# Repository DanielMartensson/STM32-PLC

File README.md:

# STM32 PLC

This project is a PCB bord that has the following measurement and control input/output:

 * 12 x ADC at 16-bit resolution for 0-20mA input with programmable gain
 * 5 x Differential ADC at 16-bit for 0-20mA input with programmable gain
 * 3 x DAC at 12-bit with 0-20mA output
 * 8 x PWM for 0-2.2A with N-channel MOSFET
 * 10 x Digital Input
 * 1 x CAN-bus channel
 * 4 x Input Capture for 0 kHz to 10kHz
 * 3 x Encoder for -32768 to 32767 pulses
 * 1 x USB port for connecting with [OpenSourceLogger](https://github.com/DanielMartensson/OpenSourceLogger) and [GoobySoft](https://github.com/DanielMartensson/GoobySoft)
 * 1 x SPI with 3 chip select for ILI9341 LCD with touch
 * 1 x ST-Link V2 connection
 * 1 x RTC clock with two alarms A(date) and B(week day) and a battery holder so the RTC remembers the date and time

## Protection 
 * All ADC, Digital Input, Differential ADC, Input Capture and Encoder are high voltage protected with PTC(fall current 30mA) fuse + 3.6v zener diode.
 * All PWM and DAC are high voltage protected with N-channel MOSFET and PNP-transistor and OP-amp. 
 * The CAN-bus channel is high voltage peak protected for 3000V under a short time with a TVS-diode. The CAN-bus transmitter itself can hold against -14V to +14V, but the TVS-diode has a limit around 6V. 

## Documentation
The documentation for the pin map can be found in the `Documentation` folder. Also all the article numbers for each component can be found in at the `DAC ADC PWM IO.sch` file in the `PCB` folder. Just double click on a PCB symbol and see the `Mouser Electronics` article number of the electrical component. 

## Calibration
Yes, it's possible to set the calibration to each input in this project. You need to have the ILI9341 touch LCD with SPI bus. Open the `STM32 PLC Pinouts.pdf` and see the connection for the LCD. You can also set the PWM frequency and analog input gain for the ADC and Differential ADC at 16-bit. 

## SAE J1939
The STM32 PLC has internal SAE J1939 protocol. Made from [Open-SAE-J1939](https://github.com/DanielMartensson/Open-SAE-J1939) repository.

## OpenSourceLogger
This is a QT C++ software that you can connect to your STM32 PLC board via the USB and then you can send signals from OpenSourceLogger and recieve signals.
OpenSourceLogger is a very easy to use logging and controlling software and it stores data at a SQL server. 

## GoobySoft
This is a ImGui C++ project that do the same as OpenSourceLogger, but it's much better and have more features. The reason why I moved away from QT C++ to ImGui C++ is because
it's much easier to write a GUI application in C++ by using ImGui instead of QT. With QT, you are stuck with object oriented programming. Everything is a class. 
But for ImGui, you can choose which type of lever you want to code, I prefer C-style C++ code with a small dose of object oriented programming (if needed). 

Consider that I will work on GoobySoft instead of OpenSourceLogger.

## Program 
The STM32 PLC has a lot of functions you can select by touching the LCD. 

 * A:Show measurement and time
 * B:Set analog gain
 * C:Set PWM frequencies
 * D:Set analog input calibration
 * E:Set pulses per encoder revolution
 * F:Set date and time and alarm
 * G:Do a PGN request
 * H:Show ECU addresses
 * I:Commanded address
 * J:Show this ECU DM1 codes
 * K:Show other ECU DM1 codes
 * L:Show this ECU DM2 codes
 * M:Show other ECU DM2 codes
 * N:Show this ECU name
 * O:Show other ECU name
 * P:Show this ECU identifications
 * Q:Show other ECU identifications
 * R:SAE J1939 Auxiliary valve command
 * S:Analog in to PWM
 * T:Analog in to analog out
 * U:About STM32 PLC

## How to build this STM32 PLC

 1. Download this repository
 2. Download & Install KiCad
 3. Open the `PCB` folder and open the `.pro` file with KiCAD and greate a `gerber` file of your own choice
 4. Go to your PCB manufacturer and give them the `gerber` file and let them produce the board for you
 5. Order the eletrical components from `Mouser Electronics`
 6. Once you have the eletrical components and your PCB board, it's time to solder them.
 7. Once the PCB board is finished, then install STM32CubeIDE
 8. Open the `Code` project and import the `.ioc` project file using STM32CubeIDE
 9. Flash the board with the `C` code by using ST-Link V2 connection
 10. Connect the ILI9431 touch LCD and then you are done!

## Software used

 * KiCAD: 6.0.7
 * STM32CubeIDE 1.10.1

## Status of the project
It's done. I don't plan to update this project. Everything is working and it will remain that way.

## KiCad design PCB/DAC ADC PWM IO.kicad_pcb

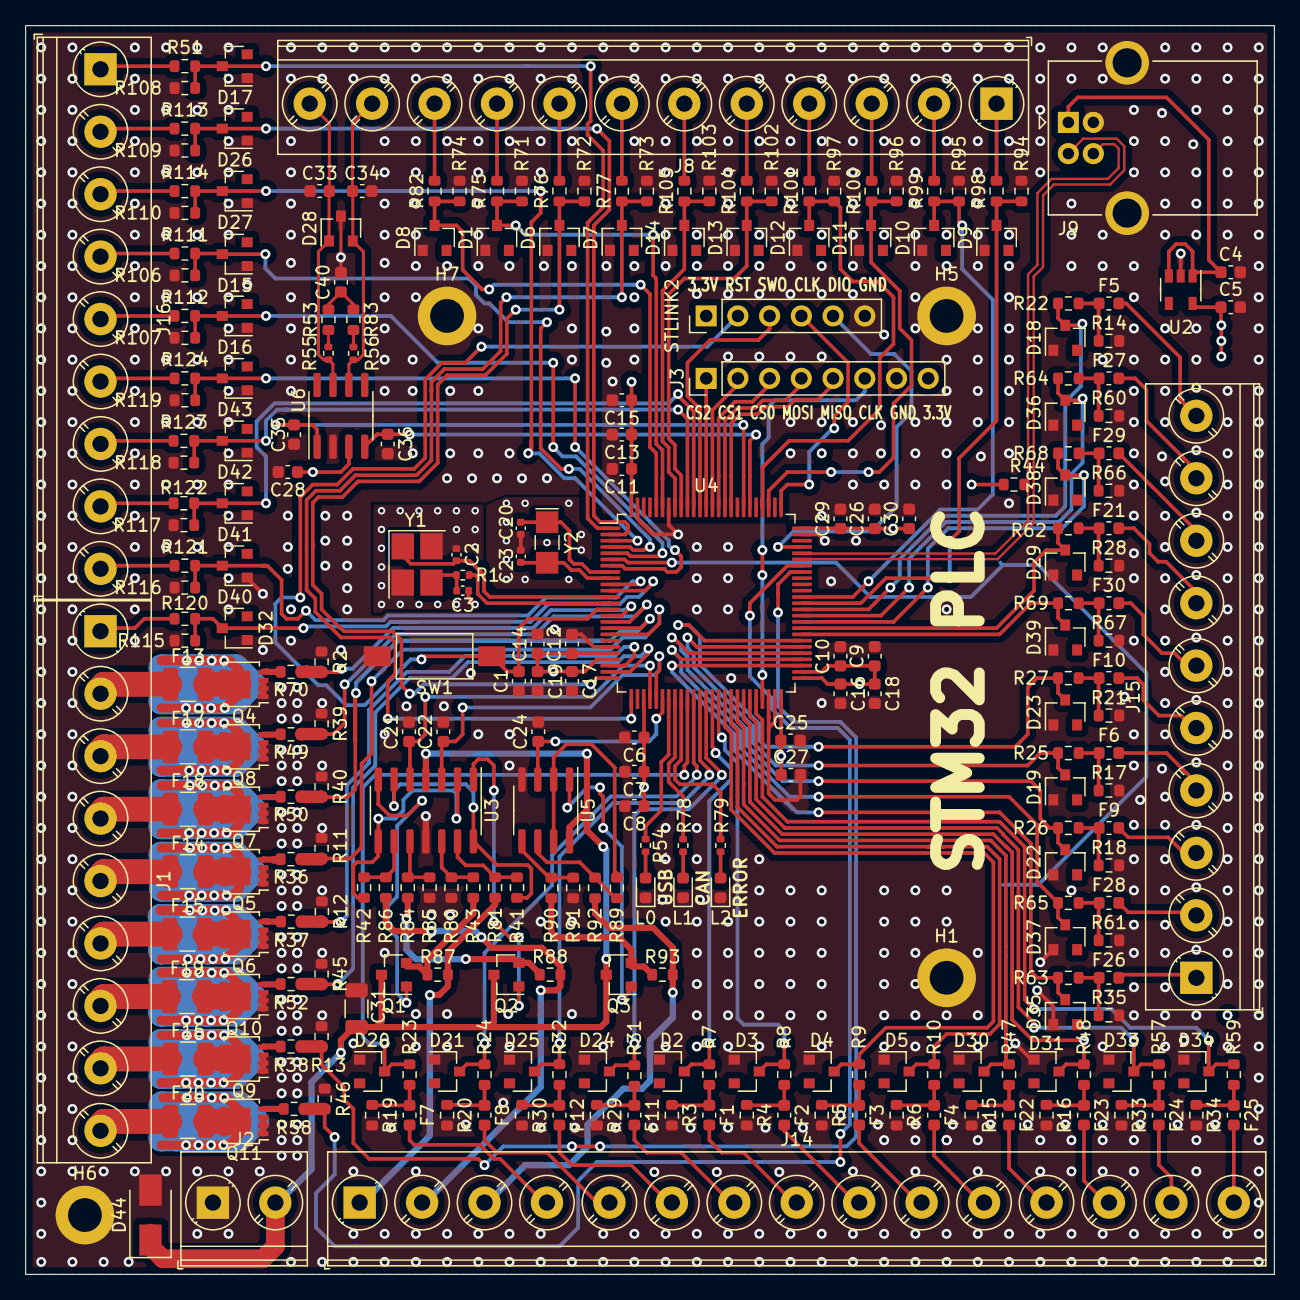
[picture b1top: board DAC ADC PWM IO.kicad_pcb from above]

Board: 4 copper layers, 100.0 x 100.0 mm, 270 parts (1 on the bottom side), 194 nets.

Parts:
BT1: Battery_Cell; BatteryHolder_Keystone_3002_1x2032
C1, C6, C7, C11, C13, C21, C22, C24, C26, C29: 100nF; C_0603_1608Metric
C2, C3: 10pF; C_0402_1005Metric
C4, C5, C9, C14, C18, C19, C27: 1uF; C_0603_1608Metric
C8, C15, C30: 4.7uF; C_0603_1608Metric
C10, C12, C16, C17, C25, C28, C33, C34, C35, C36, C40: 10nF; C_0603_1608Metric
C20, C23: 4.7pF; C_0402_1005Metric
C31: 10uF; C_1206_3216Metric
D1, D2, D3, D4, D5, D6, D7, D8, D9, D10, D11, D12, D13, D14, D15, D16, D17, D18, D19, D20, D21, D22, D23, D24, D25, D26, D27, D29, D30, D31, D32, D33, D34, D35, D36, D37, D38, D39, D40, D41, D42, D43: BZX84C3V6LT1G; D_SOT-23_ANK
D28: PESD5V0L2BT,215; SOT-23
D44: SK56A-LTP; D_SMA
F1, F2, F3, F4, F5, F6, F7, F8, F9, F10, F11, F12, F21, F22, F23, F24, F25, F26, F27, F28, F29, F30: Max 30mA; Fuse_0603_1608Metric
F13, F14, F15, F16, F17, F18, F19, F20: Max 2.5A; Fuse_1210_3225Metric
H1, H5, H6, H7: MountingHole_Pad; MountingHole_2.7mm_M2.5_DIN965_Pad
J1, J16: Screw_Terminal_01x9; TerminalBlock_Phoenix_PT-1,5-9-5.0-H_1x09_P5.00mm_Horizontal
J2: Screw_Terminal_01x02; TerminalBlock_Phoenix_PT-1,5-2-5.0-H_1x02_P5.00mm_Horizontal
J3: Conn_01x08; PinHeader_1x08_P2.54mm_Vertical
J8: Screw_Terminal_01x12; TerminalBlock_Phoenix_PT-1,5-12-5.0-H_1x12_P5.00mm_Horizont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
J9: USB_B; USB_B_OST_USB-B1HSxx_Horizontal
J14: Screw_Terminal_01x15; TerminalBlock_Phoenix_PT-1,5-15-5.0-H_1x15_P5.00mm_Horizont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
J15: Screw_Terminal_01x10; TerminalBlock_Phoenix_PT-1,5-10-5.0-H_1x10_P5.00mm_Horizont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
L0: LED_USB_RX_TX; LED_0603_1608Metric
L1: LED_CAN_RX_TX; LED_0603_1608Metric
L2: LED_ERROR; LED_0603_1608Metric
Q1, Q2, Q3: BC847C-QR; SOT-23
Q4, Q5, Q6, Q7, Q8, Q9, Q10, Q11: BUK9M15-60EX; LFPAK33
R1: 2k; R_0402_1005Metric
R2, R11, R12, R13, R39, R40, R41, R42, R43, R45, R46, R51, R62, R71, R72, R73, R74, R75, R76, R77, R80, R81, R82, R84, R85, R86, R89, R90, R91, R92, R94, R95, R96, R97, R98, R99, R100, R101, R102, R103, R104, R105, R106, R107, R108, R109, R110, R111, R112, R113, R114, R115, R116, R117, R118, R119, R120, R121, R122, R123, R124: 10k; R_0603_1608Metric
R3, R4, R5, R6, R7, R8, R9, R10, R14, R15, R16, R17, R18, R19, R20, R21, R22, R23, R24, R25, R26, R27, R28, R29, R30, R31, R32, R33, R34, R35, R36, R37, R38, R47, R48, R49, R50, R52, R57, R58, R59, R60, R61, R63, R64, R65, R66, R67, R68, R69, R70, R87, R88, R93: 160; R_0603_1608Metric
R44: 1.5k; R_0603_1608Metric
R53, R83: 60; R_0603_1608Metric
R54, R78, R79: 220; R_0402_1005Metric
R55, R56: 0; R_0402_1005Metric
STLINK2: ST-Link V2 connetor; PinHeader_1x06_P2.54mm_Vertical
SW1: SW_Push; SW_SPST_FSMSM
U2: AP7343-33W5-7; SOT-23-5
U3: LM2902; SOIC-14_3.9x8.7mm_P1.27mm
U4: STM32F373VBTx; LQFP-100_14x14mm_P0.5mm
U5: LM2904; SOIC-8_3.9x4.9mm_P1.27mm
U6: TCAN332; SOIC-8_3.9x4.9mm_P1.27mm
Y1: HSE; Crystal_SMD_3225-4Pin_3.2x2.5mm_HandSoldering
Y2: LSE; Crystal_SMD_EuroQuartz_EQ161-2Pin_3.2x1.5mm_HandSoldering

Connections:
+3V3: C5.1, C6.1, C7.1, C8.1, C9.1, C10.1, C11.1, C12.1, C13.1, C14.1, C15.1, C16.1, C17.1, C18.1, C19.1, C25.1, C26.1, C27.1, C28.1, C29.1, C30.1, J3.8, R44.2, STLINK2.1, U2.5, U4.21, U4.22, U4.28, U4.50, U4.51, U4.52, U4.75, U4.100, U6.3
+5V: C4.1, J9.1, U2.1, U2.3
/CAN/CAN+: C33.2, D28.1, J8.12, R55.1, U6.7
/CAN/CAN-: C34.1, D28.2, J8.11, R56.2, U6.6
/DAC/AO0: J14.1, R81.2, R87.2
/DAC/AO1: J14.2, R86.2, R88.2
/DAC/AO2: J14.3, R92.2, R93.2
/DSDADC/DAI0M: F28.2, J15.2
/DSDADC/DAI0P: F26.2, J15.1
/DSDADC/DAI1M: F6.2, J15.4
/DSDADC/DAI1P: F9.2, J15.3
/DSDADC/DAI2M: F30.2, J15.6
/DSDADC/DAI2P: F10.2, J15.5
/DSDADC/DAI3M: F29.2, J15.8
/DSDADC/DAI3P: F21.2, J15.7
/DSDADC/DAI4M: F5.2, J15.10
/DSDADC/DAI4P: F27.2, J15.9
/Digital/P0: F13.1, J1.2
/Digital/P1: F17.1, J1.3
/Digital/P2: F18.1, J1.4
/Digital/P3: F14.1, J1.5
/Digital/P4: F15.1, J1.6
/Digital/P5: F19.1, J1.7
/Digital/P6: F16.1, J1.8
/Digital/P7: F20.1, J1.9
/INPUT/DI0: J16.1, R51.2
/INPUT/DI1: J16.2, R113.2
/INPUT/DI2: J16.3, R114.2
/INPUT/DI3: J16.4, R111.2
/INPUT/DI4: J16.5, R112.2
/INPUT/DI5: J16.6, R124.2
/INPUT/DI6: J16.7, R123.2
/INPUT/DI7: J16.8, R122.2
/INPUT/DI8: J16.9, R121.2
/INPUT/DI9: J1.1, R120.2
/Pulse/E0+: J8.6, R105.2
/Pulse/E0-: J8.5, R104.2
/Pulse/E1+: J8.4, R101.2
/Pulse/E1-: J8.3, R100.2
/Pulse/E2+: J8.2, R99.2
/Pulse/E2-: J8.1, R98.2
/Pulse/IC0: J8.10, R82.2
/Pulse/IC1: J8.9, R75.2
/Pulse/IC2: J8.8, R76.2
/Pulse/IC3: J8.7, R77.2
/SDADC/AI0: F7.2, J14.4
/SDADC/AI1: F8.2, J14.5
/SDADC/AI2: F12.2, J14.6
/SDADC/AI3: F11.2, J14.7
/SDADC/AI4: F1.2, J14.8
/SDADC/AI5: F2.2, J14.9
/SDADC/AI6: F3.2, J14.10
/SDADC/AI7: F4.2, J14.11
/SDADC/AI8: F22.2, J14.12
/SDADC/AI9: F23.2, J14.13
/SDADC/AI10: F24.2, J14.14
/SDADC/AI11: F25.2, J14.15
GND: BT1.2, C1.1, C2.1, C3.1, C4.2, C5.2, C6.2, C7.2, C8.2, C9.2, C10.2, C11.2, C12.2, C13.2, C14.2, C15.2, C16.2, C17.2, C18.2, C19.2, C20.1, C21.2, C22.2, C23.1, C24.2, C25.2, C26.2, C27.2, C28.2, C29.2, C30.2, C31.2, C33.1, C34.2, C35.1, C36.2, C40.2, D1.2, D2.2, D3.2, D4.2, D5.2, D6.2, D7.2, D8.2, D9.2, D10.2, D11.2, D12.2, D13.2, D14.2, D15.2, D16.2, D17.2, D18.2, D19.2, D20.2, D21.2, D22.2, D23.2, D24.2, D25.2, D26.2, D27.2, D28.3, D29.2, D30.2, D31.2, D32.2, D33.2, D34.2, D35.2, D36.2, D37.2, D38.2, D39.2, D40.2, D41.2, D42.2, D43.2, D44.2, H1.1, H5.1, H6.1, H7.1, J2.1, J3.7, J9.4, J9.5, L0.1, L1.1, L2.1, Q4.1, Q4.2, Q4.3, Q5.1, Q5.2, Q5.3, Q6.1, Q6.2, Q6.3, Q7.1, Q7.2, Q7.3, Q8.1, Q8.2, Q8.3, Q9.1, Q9.2, Q9.3, Q10.1, Q10.2, Q10.3, Q11.1, Q11.2, Q11.3, R2.2, R3.2, R4.2, R5.2, R6.2, R11.2, R12.2, R13.2, R14.2, R15.2, R16.2, R17.2, R18.2, R19.2, R20.2, R21.2, R28.2, R29.2, R30.2, R33.2, R34.2, R35.2, R39.2, R40.2, R45.2, R46.2, R60.2, R61.2, R66.2, R67.2, R71.1, R72.1, R73.1, R74.1, R80.1, R85.1, R91.1, R94.1, R95.1, R96.1, R97.1, R102.1, R103.1, R106.1, R107.1, R108.1, R109.1, R110.1, R115.1, R116.1, R117.1, R118.1, R119.1, STLINK2.6, SW1.1, U2.2, U3.11, U4.20, U4.48, U4.49, U4.74, U4.94, U4.99, U5.4, U6.2, Y1.2, Y1.4
NRST: C1.2, STLINK2.2, SW1.2, U4.14
unnamed: BT1.1, U4.6
unnamed: C3.2, R1.1, Y1.3
unnamed: C40.1, R53.2, R83.1
unnamed: F1.1, R3.1, R7.1
unnamed: F2.1, R4.1, R8.1
unnamed: F3.1, R5.1, R9.1
unnamed: F4.1, R6.1, R10.1
unnamed: F5.1, R14.1, R22.1
unnamed: F6.1, R17.1, R25.1
unnamed: F7.1, R19.1, R23.1
unnamed: F8.1, R20.1, R24.1
unnamed: F9.1, R18.1, R26.1
unnamed: F10.1, R21.1, R27.1
unnamed: F11.1, R29.1, R31.1
unnamed: F12.1, R30.1, R32.1
unnamed: F13.2, Q4.5
unnamed: F14.2, Q5.5
unnamed: F15.2, Q6.5
unnamed: F16.2, Q9.5
unnamed: F17.2, Q8.5
unnamed: F18.2, Q7.5
unnamed: F19.2, Q10.5
unnamed: F20.2, Q11.5
unnamed: F21.1, R28.1, R62.1
unnamed: F22.1, R15.1, R47.1
unnamed: F23.1, R16.1, R48.1
unnamed: F24.1, R33.1, R57.1
unnamed: F25.1, R34.1, R59.1
unnamed: F26.1, R35.1, R63.1
unnamed: F27.1, R60.1, R64.1
unnamed: F28.1, R61.1, R65.1
unnamed: F29.1, R66.1, R68.1
unnamed: F30.1, R67.1, R69.1
unnamed: L0.2, R54.2
unnamed: L1.2, R78.2
unnamed: L2.2, R79.2
unnamed: Q1.1, U3.7
unnamed: Q1.2, R43.2, R87.1
unnamed: Q2.1, U3.1
unnamed: Q2.2, R84.2, R88.1
unnamed: Q3.1, U5.1
unnamed: Q3.2, R90.2, R93.1
unnamed: Q4.4, R70.2
unnamed: Q5.4, R36.2
unnamed: Q6.4, R37.2
unnamed: Q7.4, R50.2
unnamed: Q8.4, R49.2
unnamed: Q9.4, R38.2
unnamed: Q10.4, R52.2
unnamed: Q11.4, R58.2
unnamed: R41.1, U3.6, U3.14
unnamed: R41.2, R81.1, U3.13
unnamed: R42.1, U3.2, U3.8
unnamed: R42.2, R86.1, U3.9
unnamed: R43.1, R80.2, U3.12
unnamed: R53.1, R55.2
unnamed: R56.1, R83.2
unnamed: R84.1, R85.2, U3.10
unnamed: R89.1, U5.2, U5.7
unnamed: R89.2, R92.1, U5.6
unnamed: R90.1, R91.2, U5.5
PA0: R12.1, R37.1, U4.23
PA1: R45.1, R52.1, U4.24
PA2: D6.1, R72.2, R76.1, U4.25
PA3: D7.1, R73.2, R77.1, U4.26
PA4: C21.1, U3.5, U4.29
PA5: C22.1, U3.3, U4.30
PA6: C24.1, U4.31, U5.3
PA7: R54.1, U4.32
PA9: R13.1, R38.1, U4.68
PA10: R46.1, R58.1, U4.69
PA13: STLINK2.5, U4.72
PA14: STLINK2.4, U4.76
PB0: D20.1, R23.2, U4.35
PB1: D21.1, R24.2, U4.36
PB2: D25.1, R32.2, U4.37
PB3: STLINK2.3, U4.89
PB4: D41.1, R117.2, R122.1, U4.90
PB5: D42.1, R118.2, R123.1, U4.91
PB6: D13.1, R102.2, R104.1, U4.92
PB7: D14.1, R103.2, R105.1, U4.93
PB8: D1.1, R71.2, R75.1, U4.95
PB9: D8.1, R74.2, R82.1, U4.96
PB10: J3.6, U4.47
PB14: D35.1, R63.2, U4.53
PB15: D37.1, R65.2, U4.54
PC0: R2.1, R70.1, U4.15
PC1: R39.1, R49.1, U4.16
PC2: R40.1, R50.1, U4.17
PC3: R11.1, R36.1, U4.18
PC4: R78.1, U4.33
PC5: R79.1, U4.34
PC6: D9.1, R94.2, R98.1, U4.63
PC7: D10.1, R95.2, R99.1, U4.64
PC10: D11.1, R96.2, R100.1, U4.78
PC11: D12.1, R97.2, R101.1, U4.79
PC13: D43.1, R119.2, R124.1, U4.7
PC14: C20.2, U4.8, Y2.1
PC15: C23.2, U4.9, Y2.2
PD0: C36.1, U4.81, U6.4
PD1: C35.2, U4.82, U6.1
PD3: J3.5, U4.84
PD4: J3.4, U4.85
PD5: J3.3, U4.86
PD6: J3.2, U4.87
PD7: J3.1, U4.88
PD8: D22.1, R26.2, U4.55
PD9: D19.1, R25.2, U4.56
PD10: D23.1, R27.2, U4.57
PD11: D39.1, R69.2, U4.58
PD12: D29.1, R62.2, U4.59
PD13: D38.1, R68.2, U4.60
PD14: D36.1, R64.2, U4.61
PD15: D18.1, R22.2, U4.62
PE2: D17.1, R51.1, R108.2, U4.1
PE3: D26.1, R109.2, R113.1, U4.2
PE4: D27.1, R110.2, R114.1, U4.3
PE5: D15.1, R106.2, R111.1, U4.4
PE6: D16.1, R107.2, R112.1, U4.5
PE7: D24.1, R31.2, U4.38
PE8: D2.1, R7.2, U4.39
PE9: D3.1, R8.2, U4.40
PE10: D4.1, R9.2, U4.41
PE11: D5.1, R10.2, U4.42
PE12: D30.1, R47.2, U4.43
PE13: D31.1, R48.2, U4.44
PE14: D33.1, R57.2, U4.45
PE15: D34.1, R59.2, U4.46
PF0: C2.2, U4.12, Y1.1
PF1: R1.2, U4.13
PF9: D40.1, R116.2, R121.1, U4.10
PF10: D32.1, R115.2, R120.1, U4.11
USB+: J9.3, R44.1, U4.71
USB-: J9.2, U4.70
VDC: C31.1, D44.1, J2.2, Q1.3, Q2.3, Q3.3, U3.4, U5.8

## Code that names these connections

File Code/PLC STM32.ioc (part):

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Mcu.Name=STM32F373V(8-B-C)Tx
Mcu.Package=LQFP100
Mcu.UserName=STM32F373VBTx
PA0.GPIOParameters=GPIO_Label
PA0.GPIO_Label=PWM4
PA0.Signal=S_TIM2_CH1_ETR
PA1.GPIOParameters=GPIO_Label
PA1.GPIO_Label=PWM5
PA1.Signal=S_TIM2_CH2
PA10.GPIOParameters=GPIO_Label
PA10.GPIO_Label=PWM7
PA10.Signal=S_TIM2_CH4
PA11.Mode=Device
PA11.Signal=USB_DM
PA12.Mode=Device
PA12.Signal=USB_DP
PA13.Mode=Trace_Asynchronous_SW
PA13.Signal=SYS_JTMS-SWDIO
PA14.Mode=Trace_Asynchronous_SW
PA14.Signal=SYS_JTCK-SWCLK
PA2.GPIOParameters=GPIO_Label
PA2.GPIO_Label=IC2
PA2.Signal=S_TIM15_CH1
PA3.GPIOParameters=GPIO_Label
PA3.GPIO_Label=IC3
PA3.Signal=S_TIM15_CH2
PA4.GPIOParameters=GPIO_Label
PA4.GPIO_Label=AO0
PA4.Signal=COMP_DAC11_group
PA5.GPIOParameters=GPIO_Label
PA5.GPIO_Label=AO1
PA5.Signal=COMP_DAC12_group
PA6.GPIOParameters=GPIO_Label
PA6.GPIO_Label=AO2
PA6.Signal=COMP_DAC21_group
PA7.GPIOParameters=GPIO_Label
PA7.GPIO_Label=LED_USB
PA7.Signal=GPIO_Output
PA9.GPIOParameters=GPIO_Label
PA9.GPIO_Label=PWM6
PA9.Signal=S_TIM2_CH3
PB0.GPIOParameters=GPIO_Label
PB0.GPIO_Label=AI0
PB0.Mode=IN6-Single-Ended zero reference
PB0.Signal=SDADC1_AIN6P
PB1.GPIOParameters=GPIO_Label
PB1.GPIO_Label=AI1
PB1.Mode=IN5-Single-Ended zero reference
PB1.Signal=SDADC1_AIN5P
PB10.Mode=Full_Duplex_Master
PB10.Signal=SPI2_SCK
PB14.GPIOParameters=GPIO_Label
PB14.GPIO_Label=DAI0P
PB14.Mode=IN8-Differential
PB14.Signal=SDADC3_AIN8P
PB15.GPIOParameters=GPIO_Label
PB15.GPIO_Label=DAI0M
PB15.Mode=IN8-Differential
PB15.Signal=SDADC3_AIN8M
PB2.GPIOParameters=GPIO_Label
PB2.GPIO_Label=AI2
PB2.Mode=IN4-Single-Ended zero reference
PB2.Signal=SDADC1_AIN4P
PB3.Mode=Trace_Asynchronous_SW
PB3.Signal=SYS_JTDO-TRACESWO
PB4.GPIOParameters=GPIO_Label
PB4.GPIO_Label=DI7
PB4.Signal=GPIO_Input
PB5.GPIOParameters=GPIO_Label
PB5.GPIO_Label=DI6
PB5.Signal=GPIO_Input
PB6.GPIOParameters=GPIO_Label
PB6.GPIO_Label=E0-
PB6.Signal=S_TIM4_CH1
PB7.GPIOParameters=GPIO_Label
PB7.GPIO_Label=E0+
PB7.Signal=S_TIM4_CH2
PB8.GPIOParameters=GPIO_Label
PB8.GPIO_Label=IC1
PB8.Signal=S_TIM16_CH1
PB9.GPIOParameters=GPIO_Label
PB9.GPIO_Label=IC0
PB9.Signal=S_TIM17_CH1
PC0.GPIOParameters=GPIO_Label
PC0.GPIO_Label=PWM0
PC0.Signal=S_TIM5_CH1_ETR
PC1.GPIOParameters=GPIO_Label
PC1.GPIO_Label=PWM1
PC1.Signal=S_TIM5_CH2
PC10.GPIOParameters=GPIO_Label
PC10.GPIO_Label=E1-
PC10.Signal=S_TIM19_CH1
PC11.GPIOParameters=GPIO_Label
PC11.GPIO_Label=E1+
PC11.Signal=S_TIM19_CH2
PC13.GPIOParameters=GPIO_PuPd,GPIO_Label
PC13.GPIO_Label=DI5
PC13.GPIO_PuPd=GPIO_PULLDOWN
PC13.Signal=GPIO_Input
PC14-OSC32_IN.Mode=LSE-External-Oscillator
PC14-OSC32_IN.Signal=RCC_OSC32_IN
PC15-OSC32_OUT.Mode=LSE-External-Oscillator
PC15-OSC32_OUT.Signal=RCC_OSC32_OUT
PC2.GPIOParameters=GPIO_Label
PC2.GPIO_Label=PWM2
PC2.Signal=S_TIM5_CH3
PC3.GPIOParameters=GPIO_Label
PC3.GPIO_Label=PWM3
PC3.Signal=S_TIM5_CH4
PC4.GPIOParameters=GPIO_Label
PC4.GPIO_Label=LED_CAN
PC4.Signal=GPIO_Output
PC5.GPIOParameters=GPIO_Label
PC5.GPIO_Label=LED_ERROR
PC5.Signal=GPIO_Output
PC6.GPIOParameters=GPIO_Label
PC6.GPIO_Label=E2-
PC6.Signal=S_TIM3_CH1
PC7.GPIOParameters=GPIO_Label
PC7.GPIO_Label=E2+
PC7.Signal=S_TIM3_CH2
PD0.Mode=CAN_Activate
PD0.Signal=CAN_RX
PD1.Mode=CAN_Activate
PD1.Signal=CAN_TX
PD10.GPIOParameters=GPIO_Label
PD10.GPIO_Label=DAI2P
PD10.Mode=IN4-Differential
PD10.Signal=SDADC3_AIN4P
PD11.GPIOParameters=GPIO_Label
PD11.GPIO_Label=DAI2M
PD11.Mode=IN4-Differential
PD11.Signal=SDADC3_AIN4M
PD12.GPIOParameters=GPIO_Label
PD12.GPIO_Label=DAI3P
PD12.Mode=IN2-Differential
PD12.Signal=SDADC3_AIN2P
PD13.GPIOParameters=GPIO_Label
PD13.GPIO_Label=DAI3M
PD13.Mode=IN2-Differential
PD13.Signal=SDADC3_AIN2M
PD14.GPIOParameters=GPIO_Label
PD14.GPIO_Label=DAI4P
PD14.Mode=IN0-Differential
PD14.Signal=SDADC3_AIN0P
PD15.GPIOParameters=GPIO_Label
PD15.GPIO_Label=DAI4M
PD15.Mode=IN0-Differential
PD15.Signal=SDADC3_AIN0M
PD3.Mode=Full_Duplex_Master
PD3.Signal=SPI2_MISO
PD4.Mode=Full_Duplex_Master
PD4.Signal=SPI2_MOSI
PD5.GPIOParameters=GPIO_Label
PD5.GPIO_Label=CS0
PD5.Signal=GPIO_Output
PD6.GPIOParameters=GPIO_Label
PD6.GPIO_Label=CS1
PD6.Signal=GPIO_Output
PD7.GPIOParameters=GPIO_Label
PD7.GPIO_Label=CS2
PD7.Signal=GPIO_Output
PD8.GPIOParameters=GPIO_Label
PD8.GPIO_Label=DAI1P
PD8.Mode=IN6-Differential
PD8.Signal=SDADC3_AIN6P
PD9.GPIOParameters=GPIO_Label
PD9.GPIO_Label=DAI1M
PD9.Mode=IN6-Differential
PD9.Signal=SDADC3_AIN6M
PE10.GPIOParameters=GPIO_Label
PE10.GPIO_Label=AI6
PE10.Mode=IN2-Single-Ended zero reference
PE10.Signal=SDADC1_AIN2P
PE11.GPIOParameters=GPIO_Label
PE11.GPIO_Label=AI7
PE11.Mode=IN1-Single-Ended zero reference
PE11.Signal=SDADC1_AIN1P
PE12.GPIOParameters=GPIO_Label
PE12.GPIO_Label=AI8
PE12.Mode=IN0-Single-Ended zero reference
PE12.Signal=SDADC1_AIN0P
PE13.GPIOParameters=GPIO_Label
PE13.GPIO_Label=AI9
PE13.Mode=IN2-Single-Ended zero reference
PE13.Signal=SDADC2_AIN2P
PE14.GPIOParameters=GPIO_Label
PE14.GPIO_Label=AI10
PE14.Mode=IN1-Single-Ended zero reference
PE14.Signal=SDADC2_AIN1P
PE15.GPIOParameters=GPIO_Label
PE15.GPIO_Label=AI11
PE15.Mode=IN0-Single-Ended zero reference
PE15.Signal=SDADC2_AIN0P
PE2.GPIOParameters=GPIO_PuPd,GPIO_Label
PE2.GPIO_Label=DI0
PE2.GPIO_PuPd=GPIO_PULLDOWN
PE2.Signal=GPIO_Input
PE3.GPIOParameters=GPIO_PuPd,GPIO_Label
PE3.GPIO_Label=DI1
PE3.GPIO_PuPd=GPIO_PULLDOWN
PE3.Signal=GPIO_Input
PE4.GPIOParameters=GPIO_PuPd,GPIO_Label
PE4.GPIO_Label=DI2
PE4.GPIO_PuPd=GPIO_PULLDOWN
PE4.Signal=GPIO_Input
PE5.GPIOParameters=GPIO_PuPd,GPIO_Label
PE5.GPIO_Label=DI3
PE5.GPIO_PuPd=GPIO_PULLDOWN
PE5.Signal=GPIO_Input
PE6.GPIOParameters=GPIO_PuPd,GPIO_Label
PE6.GPIO_Label=DI4
PE6.GPIO_PuPd=GPIO_PULLDOWN
PE6.Signal=GPIO_Input
PE7.GPIOParameters=GPIO_Label
PE7.GPIO_Label=AI3
PE7.Mode=IN3-Single-Ended zero reference
PE7.Signal=SDADC1_AIN3P
PE8.GPIOParameters=GPIO_Label
PE8.GPIO_Label=AI4
PE8.Mode=IN8-Single-Ended zero reference
PE8.Signal=SDADC1_AIN8P
PE9.GPIOParameters=GPIO_Label
PE9.GPIO_Label=AI5
PE9.Mode=IN7-Single-Ended zero reference
PE9.Signal=SDADC1_AIN7P
PF0-OSC_IN.Mode=HSE-External-Oscillator
PF0-OSC_IN.Signal=RCC_OSC_IN
PF1-OSC_OUT.Mode=HSE-External-Oscillator
PF1-OSC_OUT.Signal=RCC_OSC_OUT
PF10.GPIOParameters=GPIO_PuPd,GPIO_Label
PF10.GPIO_Label=DI9
PF10.GPIO_PuPd=GPIO_PULLDOWN
PF10.Signal=GPIO_Input
PF9.GPIOParameters=GPIO_PuPd,GPIO_Label
PF9.GPIO_Label=DI8
PF9.GPIO_PuPd=GPIO_PULLDOWN
PF9.Signal=GPIO_Input
RCC.HSEPLLFreq_Value=8000000
RCC.HSE_Timout=100
RCC.HSE_VALUE=8000000
RCC.SYSCLKFreq_VALUE=48000000
RCC.SYSCLKSource=RCC_SYSCLKSOURCE_PLLCLK
board=custom

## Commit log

2022-05-28 Done!
2022-05-28 Create LICENSE
2022-05-30 Add blueprints for shell
2022-05-31 LCD holder
2022-12-20 Update CAN-bus configuration
2023-08-20 Upload for GoobySoft
2023-08-20 Update readme about GoobySoft
2023-08-20 Change about screen for GoobySoft
2023-08-24 Update README.md with GoobySoft
